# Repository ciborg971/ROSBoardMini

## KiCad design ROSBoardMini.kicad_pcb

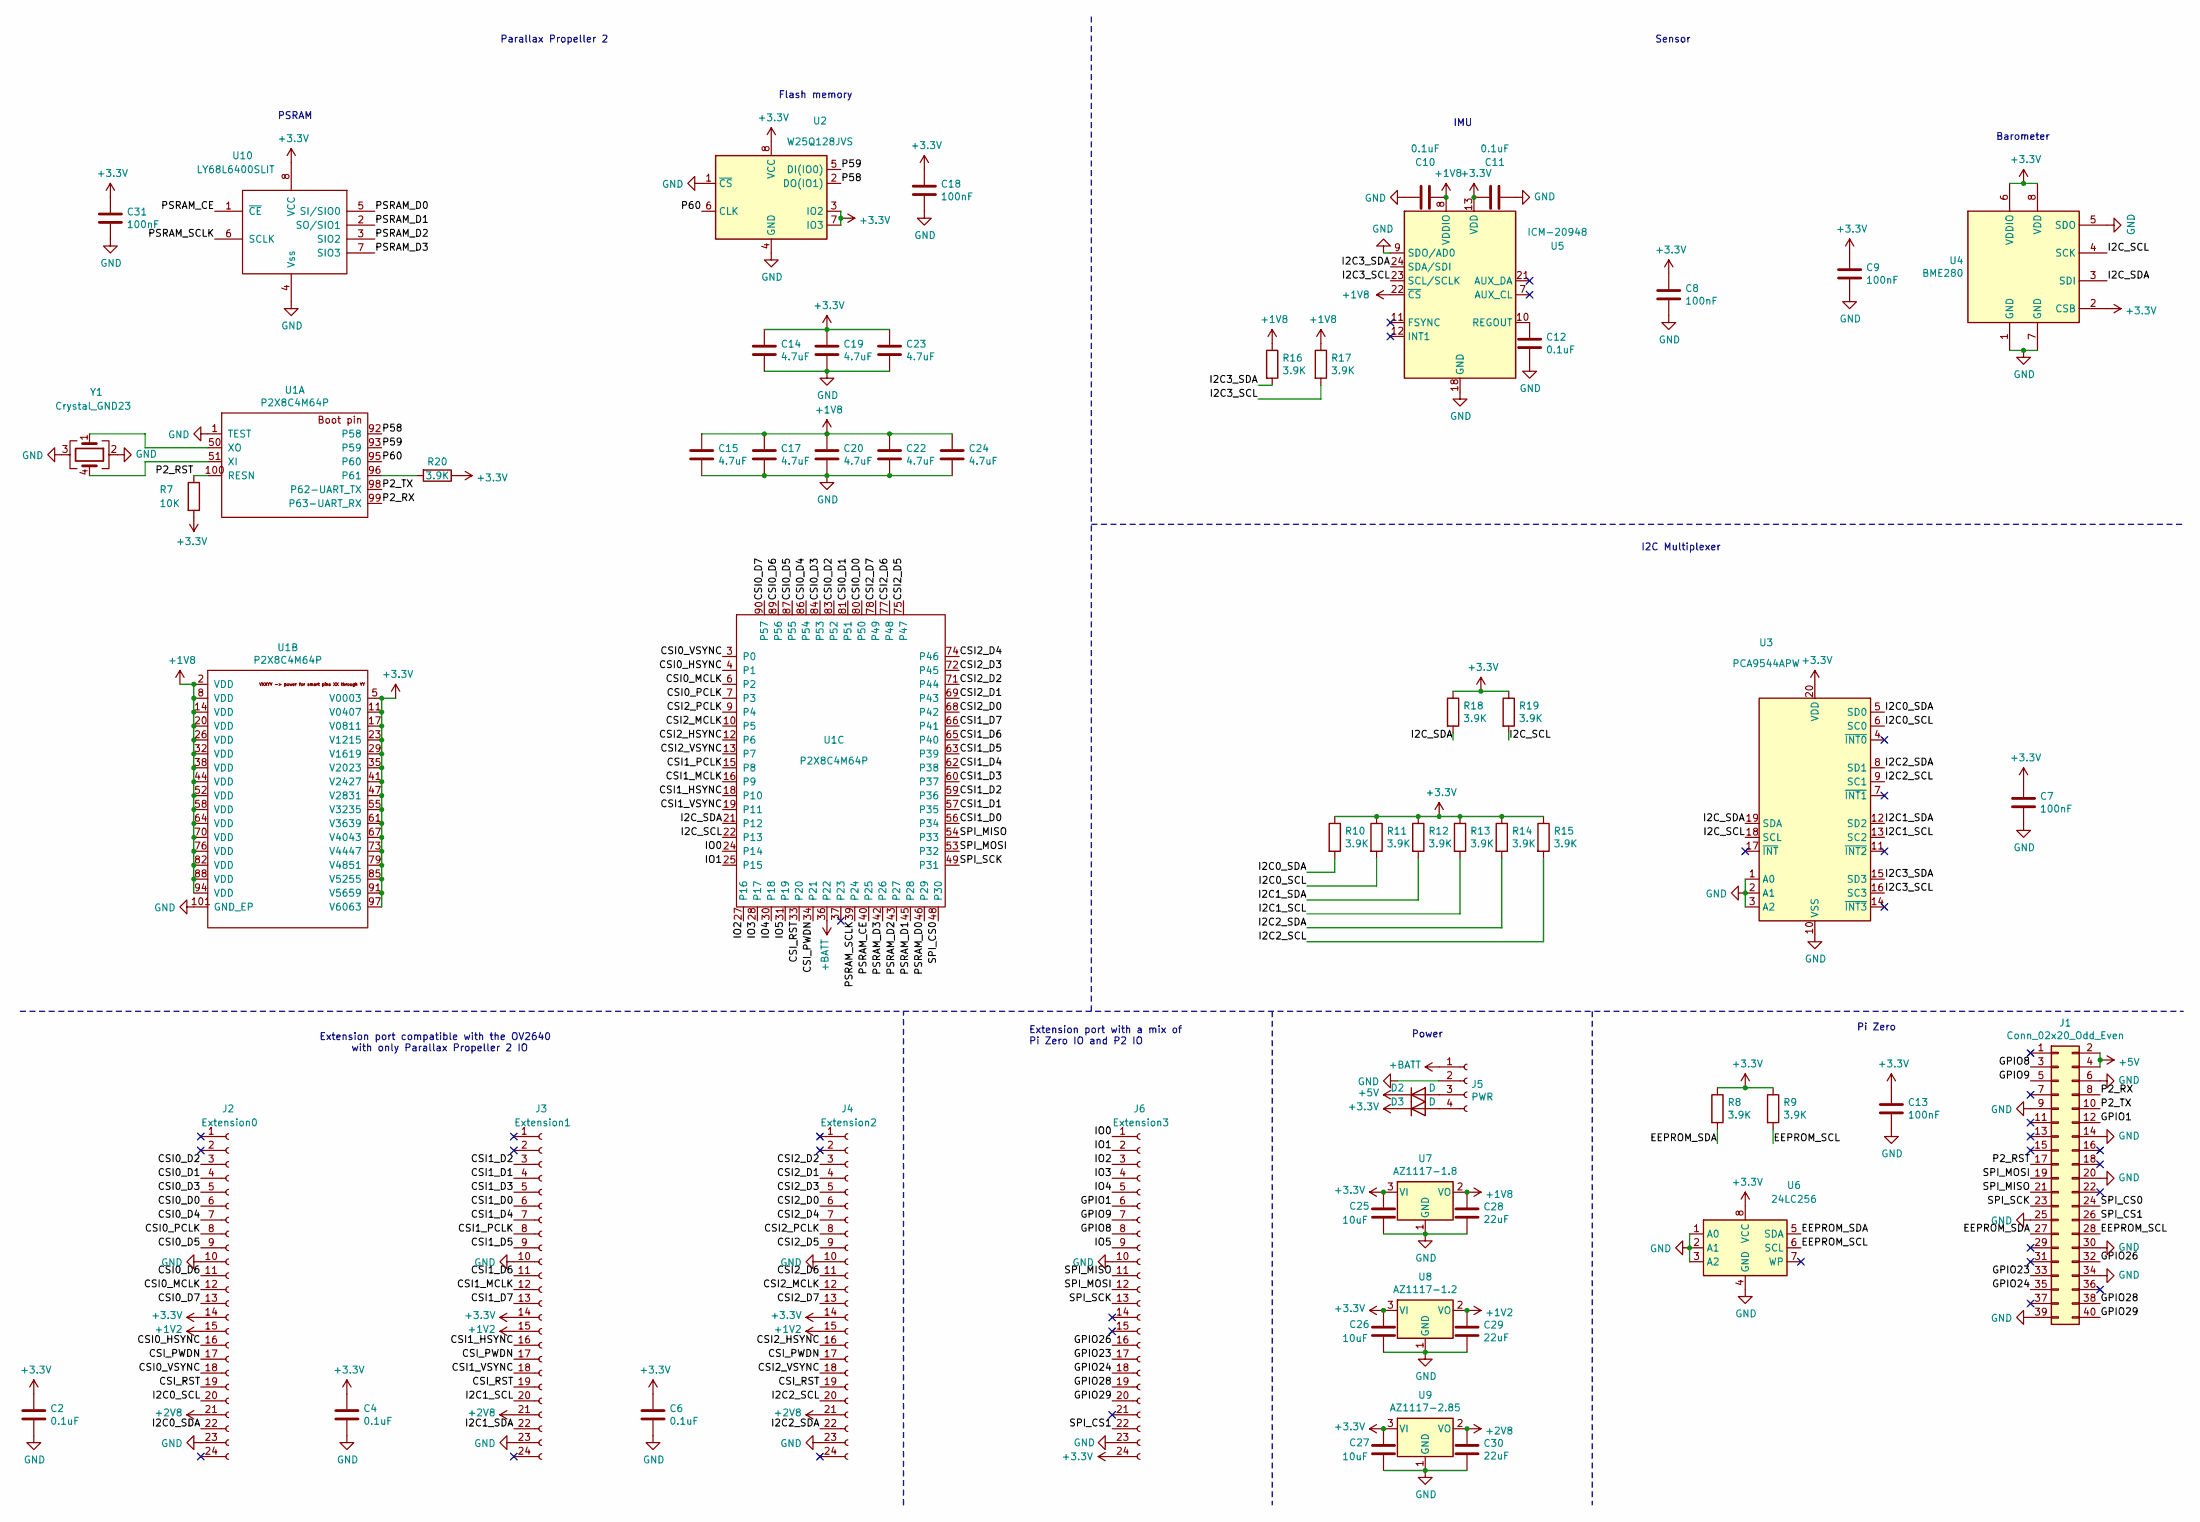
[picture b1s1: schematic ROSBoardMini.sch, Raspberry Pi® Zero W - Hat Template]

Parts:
C2, C4, C6, C10, C11, C12: 0.1uF; C_0402_1005Metric
C7, C8, C9, C13, C18, C31: 100nF; C_0402_1005Metric
C14, C15, C17, C19, C20, C22, C23, C24: 4.7uF; C_0402_1005Metric
C25, C26, C27: 10uF; C_0402_1005Metric
C28, C29, C30: 22uF; C_0402_1005Metric
D2, D3: D; D_0805_2012Metric
J1: Conn_02x20_Odd_Even; PinHeader_2x20_P2.54mm_Vertical
J2: Extension0; Hirose_FH12-24S-0.5SH_1x24-1MP_P0.50mm_Horizontal
J3: Extension1; Hirose_FH12-24S-0.5SH_1x24-1MP_P0.50mm_Horizontal
J4: Extension2; Hirose_FH12-24S-0.5SH_1x24-1MP_P0.50mm_Horizontal
J5: PWR; PinHeader_1x04_P2.54mm_Vertical
J6: Extension3; Hirose_FH12-24S-0.5SH_1x24-1MP_P0.50mm_Horizontal
R7: 10K; R_0201_0603Metric
R8, R9, R10, R11, R12, R13, R14, R15, R16, R17, R18, R19, R20: 3.9K; R_0201_0603Metric
U1: P2X8C4M64P; TQFP-100-1EP_14x14mm_P0.5mm_EP5x5mm
U2: W25Q128JVS; SOIC-8_5.23x5.23mm_P1.27mm
U3: PCA9544APW; TSSOP-20_4.4x6.5mm_P0.65mm
U4: BME280; Bosch_LGA-8_2.5x2.5mm_P0.65mm_ClockwisePinNumbering
U5: ICM-20948; InvenSense_QFN-24_3x3mm_P0.4mm
U6: 24LC256; TSSOP-8_4.4x3mm_P0.65mm
U7: AZ1117-1.8; SOT-89-3
U8: AZ1117-1.2; SOT-89-3
U9: AZ1117-2.85; SOT-89-3
U10: LY68L6400SLIT; SOP-8_3.9x4.9mm_P1.27mm
Y1: Crystal_GND23; Crystal_SMD_Abracon_ABM8G-4Pin_3.2x2.5mm

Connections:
+1V2: C29.1, J2.15, J3.15, J4.15, U8.2 (VO)
+1V8: C10.1, C15.1, C17.1, C20.1, C22.1, C24.1, C28.1, R16.1, R17.1, U1.2 (VDD), U1.8 (VDD), U1.14 (VDD), U1.20 (VDD), U1.26 (VDD), U1.32 (VDD), U1.38 (VDD), U1.44 (VDD), U1.52 (VDD), U1.58 (VDD), U1.64 (VDD), U1.70 (VDD), U1.76 (VDD), U1.82 (VDD), U1.88 (VDD), U1.94 (VDD), U5.8 (VDDIO), U5.22 (~CS), U7.2 (VO)
+5V: D2.1 (K), J1.2, J1.4
+BATT: J5.1, U1.36 (P22)
/CSI0_D0: J2.6, U1.80 (P50)
/CSI0_D1: J2.4, U1.81 (P51)
/CSI0_D2: J2.3, U1.83 (P52)
/CSI0_D3: J2.5, U1.84 (P53)
/CSI0_D4: J2.7, U1.86 (P54)
/CSI0_D5: J2.9, U1.87 (P55)
/CSI0_D6: J2.11, U1.89 (P56)
/CSI0_D7: J2.13, U1.90 (P57)
/CSI0_HSYNC: J2.16, U1.4 (P1)
/CSI0_MCLK: J2.12, U1.6 (P2)
/CSI0_PCLK: J2.8, U1.7 (P3)
/CSI0_VSYNC: J2.18, U1.3 (P0)
/CSI1_D0: J3.6, U1.56 (P34)
/CSI1_D1: J3.4, U1.57 (P35)
/CSI1_D2: J3.3, U1.59 (P36)
/CSI1_D3: J3.5, U1.60 (P37)
/CSI1_D4: J3.7, U1.62 (P38)
/CSI1_D5: J3.9, U1.63 (P39)
/CSI1_D6: J3.11, U1.65 (P40)
/CSI1_D7: J3.13, U1.66 (P41)
/CSI1_HSYNC: J3.16, U1.18 (P10)
/CSI1_MCLK: J3.12, U1.16 (P9)
/CSI1_PCLK: J3.8, U1.15 (P8)
/CSI1_VSYNC: J3.18, U1.19 (P11)
/CSI2_D0: J4.6, U1.68 (P42)
/CSI2_D1: J4.4, U1.69 (P43)
/CSI2_D2: J4.3, U1.71 (P44)
/CSI2_D3: J4.5, U1.72 (P45)
/CSI2_D4: J4.7, U1.74 (P46)
/CSI2_D5: J4.9, U1.75 (P47)
/CSI2_D6: J4.11, U1.77 (P48)
/CSI2_D7: J4.13, U1.78 (P49)
/CSI2_HSYNC: J4.16, U1.12 (P6)
/CSI2_MCLK: J4.12, U1.10 (P5)
/CSI2_PCLK: J4.8, U1.9 (P4)
/CSI2_VSYNC: J4.18, U1.13 (P7)
/CSI_PWDN: J2.17, J3.17, J4.17, U1.34 (P21)
/CSI_RST: J2.19, J3.19, J4.19, U1.33 (P20)
/EEPROM_SCL: J1.28, R9.2, U6.6 (SCL)
/EEPROM_SDA: J1.27, R8.2, U6.5 (SDA)
/GPIO1: J1.12, J6.6
/GPIO8: J1.3, J6.8
/GPIO9: J1.5, J6.7
/GPIO23: J1.33, J6.17
/GPIO24: J1.35, J6.18
/GPIO26: J1.32, J6.16
/GPIO28: J1.38, J6.19
/GPIO29: J1.40, J6.20
/I2C0_SCL: J2.20, R11.2, U3.6 (SC0)
/I2C0_SDA: J2.22, R10.2, U3.5 (SD0)
/I2C1_SCL: J3.20, R13.2, U3.13 (SC2)
/I2C1_SDA: J3.22, R12.2, U3.12 (SD2)
/I2C2_SCL: J4.20, R15.2, U3.9 (SC1)
/I2C2_SDA: J4.22, R14.2, U3.8 (SD1)
/I2C3_SCL: R17.2, U3.16 (SC3), U5.23 (SCL/SCLK)
/I2C3_SDA: R16.2, U3.15 (SD3), U5.24 (SDA/SDI)
/I2C_SCL: R19.2, U1.22 (P13), U3.18 (SCL), U4.4 (SCK)
/I2C_SDA: R18.2, U1.21 (P12), U3.19 (SDA), U4.3 (SDI)
/IO0: J6.1, U1.24 (P14)
/IO1: J6.2, U1.25 (P15)
/IO2: J6.3, U1.27 (P16)
/IO3: J6.4, U1.28 (P17)
/IO4: J6.5, U1.30 (P18)
/IO5: J6.9, U1.31 (P19)
/P2_RST: J1.17, R7.1, U1.100 (RESN)
/P2_RX: J1.8, U1.99 (P63-UART_RX)
/P2_TX: J1.10, U1.98 (P62-UART_TX)
/P58: U1.92 (P58), U2.2 (DO(IO1))
/P59: U1.93 (P59), U2.5 (DI(IO0))
/P60: U1.95 (P60), U2.6 (CLK)
/PSRAM_CE: U1.40 (P25), U10.1 (~CE)
/PSRAM_D0: U1.46 (P29), U10.5 (SI/SIO0)
/PSRAM_D1: U1.45 (P28), U10.2 (SO/SIO1)
/PSRAM_D2: U1.43 (P27), U10.3 (SIO2)
/PSRAM_D3: U1.42 (P26), U10.7 (SIO3)
/PSRAM_SCLK: U1.39 (P24), U10.6 (SCLK)
/SPI_CS0: J1.24, U1.48 (P30)
/SPI_CS1: J1.26, J6.22
/SPI_MISO: J1.21, J6.11, U1.54 (P33)
/SPI_MOSI: J1.19, J6.12, U1.53 (P32)
/SPI_SCK: J1.23, J6.13, U1.49 (P31)
unnamed 85: U9.6; also elsewhere on the board
unnamed: C12.1, U5.10 (REGOUT)
unnamed: D2.2 (A), J5.3
unnamed: D3.2 (A), J5.4
unnamed: R20.2, U1.96 (P61)
unnamed: U1.50 (XO), Y1.1
unnamed: U1.51 (XI), Y1.4

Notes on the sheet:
Extension port compatible with the OV2640 with only Parallax Propeller 2 IO
Extension port with a mix of Pi Zero IO and P2 IO
Power
I2C Multiplexer
Sensor
Pi Zero
Parallax Propeller 2
Flash memory
PSRAM
Barometer
IMU

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
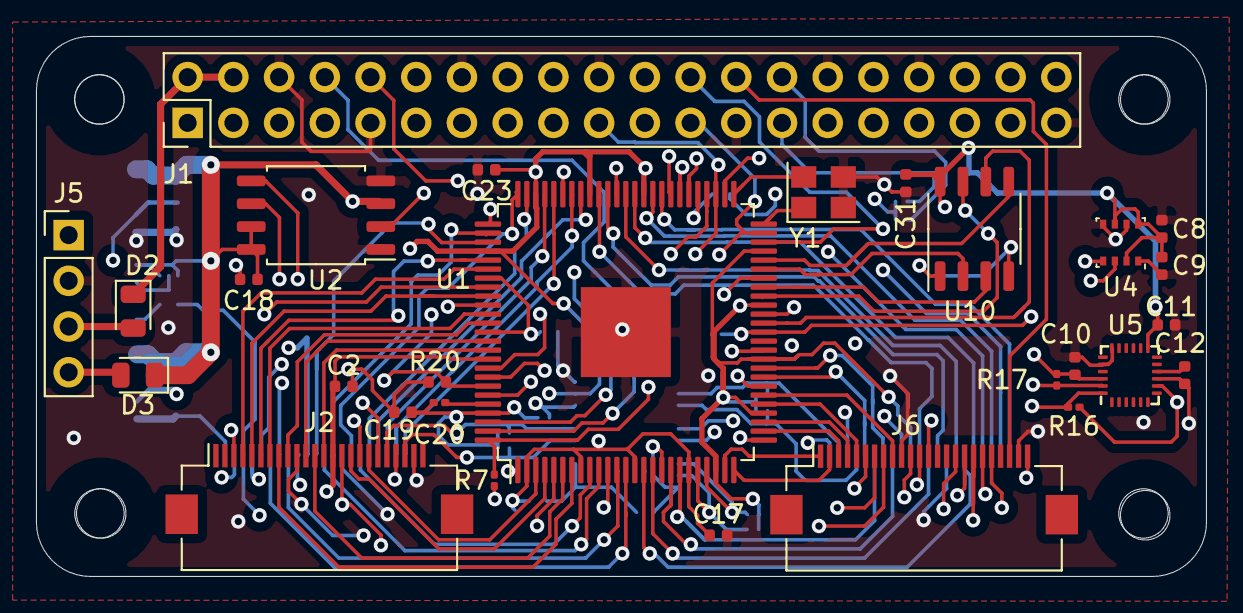
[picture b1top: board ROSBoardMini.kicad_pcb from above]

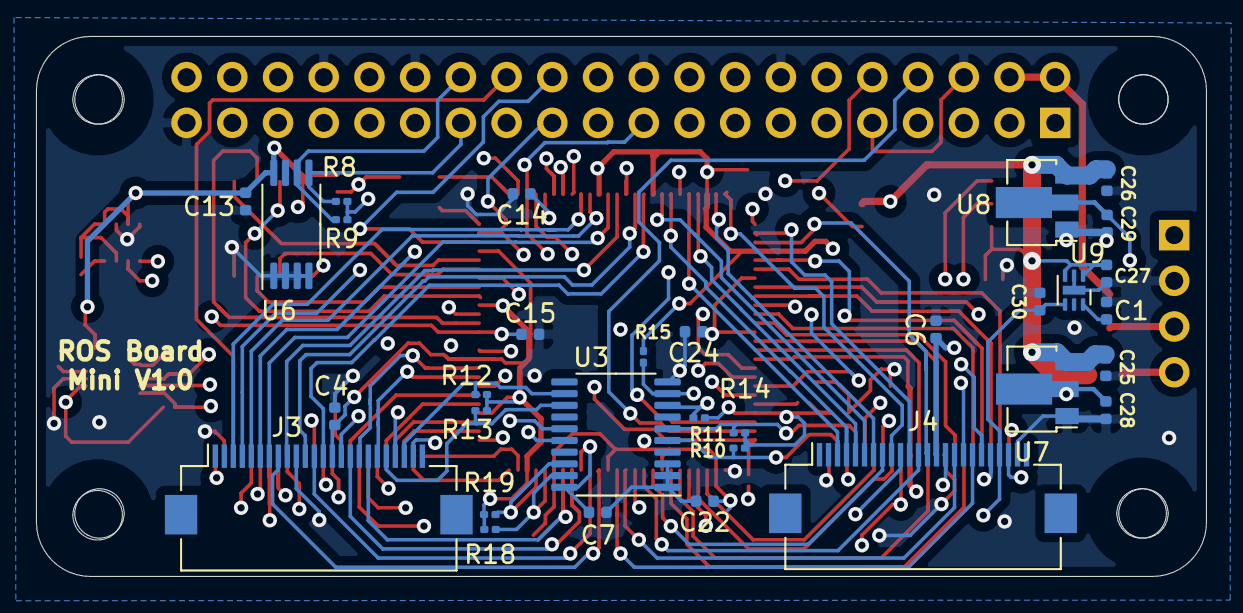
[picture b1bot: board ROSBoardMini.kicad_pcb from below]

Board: 4 copper layers, 65.0 x 30.0 mm, 60 parts (32 on the bottom side), 95 nets.

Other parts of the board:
C1: 0.1uF; C_0402_1005Metric

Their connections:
unnamed 85: C1.1; also elsewhere on the board

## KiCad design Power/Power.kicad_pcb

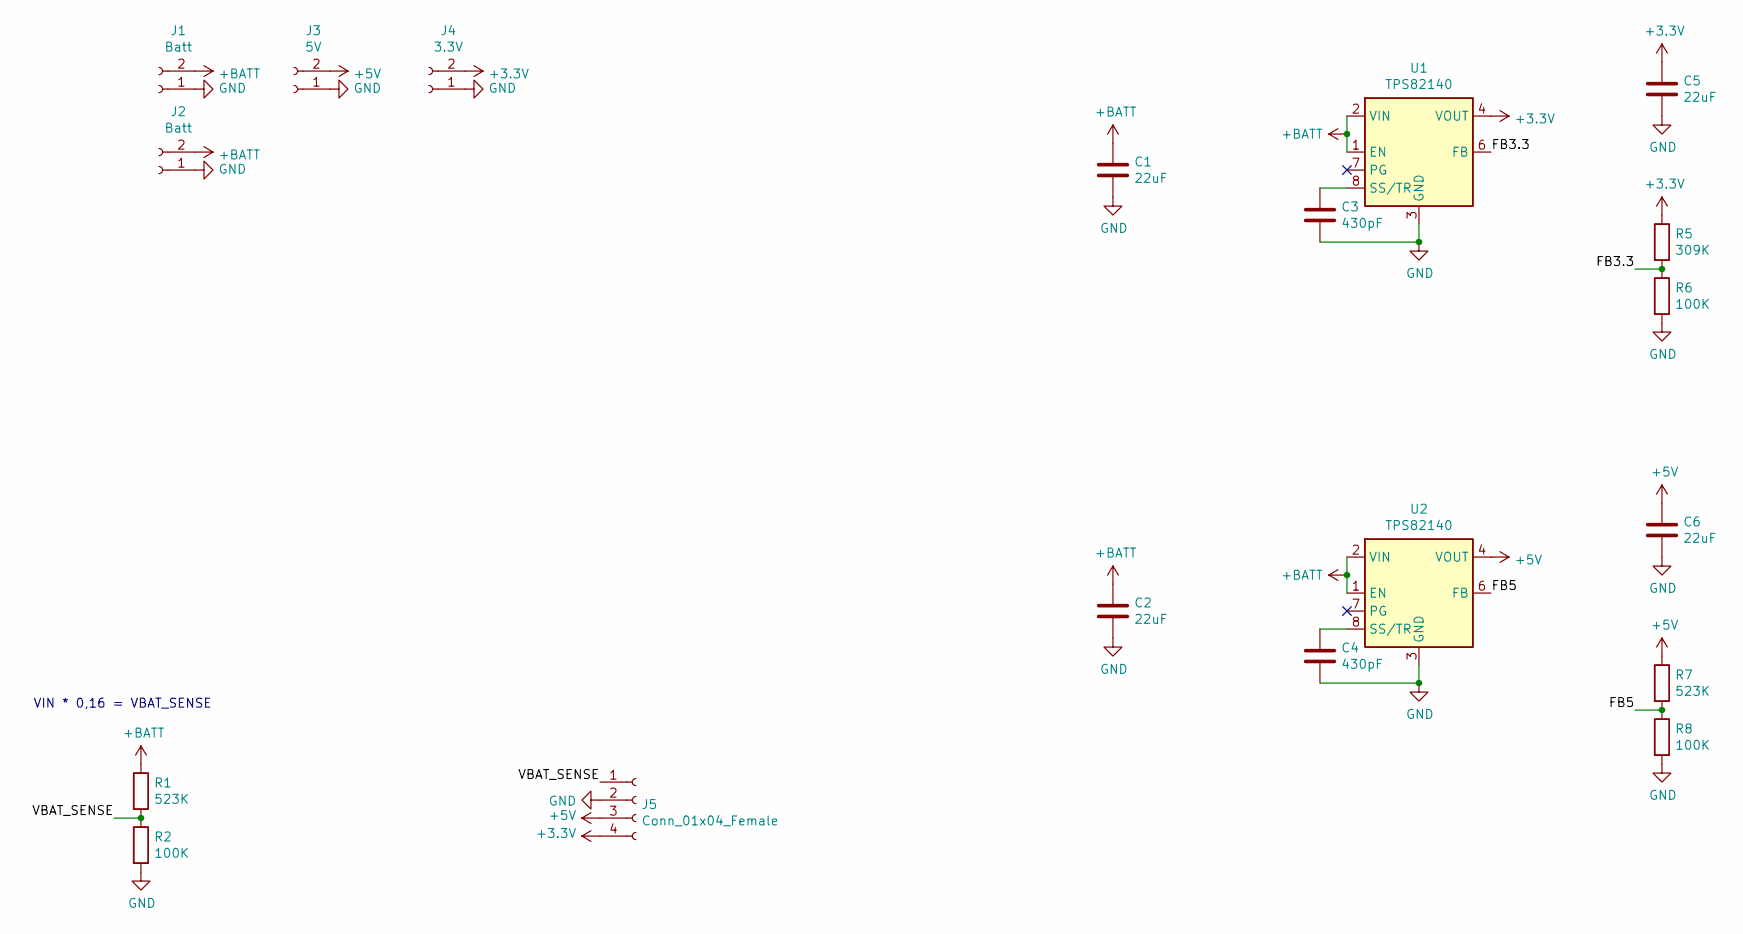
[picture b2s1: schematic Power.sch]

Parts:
C1, C2, C5, C6: 22uF; C_0402_1005Metric
C3, C4: 430pF; C_0402_1005Metric
J1, J2: Batt; PinSocket_1x02_P2.54mm_Vertical
J3: 5V; PinSocket_1x02_P2.54mm_Vertical
J4: 3.3V; PinSocket_1x02_P2.54mm_Vertical
J5: Conn_01x04_Female; PinSocket_1x04_P2.54mm_Vertical
R1, R7: 523K; R_0402_1005Metric
R2, R6, R8: 100K; R_0402_1005Metric
R5: 309K; R_0402_1005Metric
U1, U2: TPS82140; Texas_SIL0008D_MicroSiP-8-1EP_2.8x3mm_P0.65mm_EP1.1x1.9mm_T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

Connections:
+3V3: C5.1, J4.2, J5.4, R5.1, U1.4 (VOUT), U1.5 (VOUT)
+5V: C6.1, J3.2, J5.3, R7.1, U2.4 (VOUT), U2.5 (VOUT)
+BATT: C1.1, C2.1, J1.2, J2.2, R1.1, U1.1 (EN), U1.2 (VIN), U2.1 (EN), U2.2 (VIN)
/FB3.3: R5.2, R6.1, U1.6 (FB)
/FB5: R7.2, R8.1, U2.6 (FB)
/VBAT_SENSE: J5.1, R1.2, R2.1
GND: C1.2, C2.2, C3.2, C4.2, C5.2, C6.2, J1.1, J2.1, J3.1, J4.1, J5.2, R2.2, R6.2, R8.2, U1.3 (GND), U1.9 (GND), U2.3 (GND), U2.9 (GND)
unnamed: C3.1, U1.8 (SS/TR)
unnamed: C4.1, U2.8 (SS/TR)

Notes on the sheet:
VIN * 0,16 = VBAT_SENSE

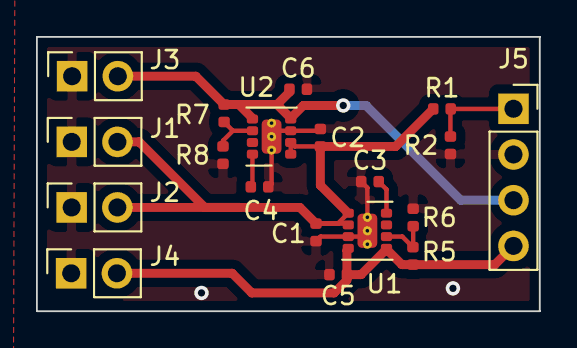
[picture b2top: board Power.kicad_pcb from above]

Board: 2 copper layers, 27.9 x 15.2 mm, 19 parts (0 on the bottom side), 9 nets.

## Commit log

2020-10-29 add lib and doc
2020-10-29 Rooting progress
2020-11-02 Re arrange pin to allow 1 cog to use 3 camera + rooting progress
2020-11-02 Everything rooted except power
2020-11-02 Extension board for breadboard
2020-11-03 Rooting done
2020-11-04 Power board done
2020-11-04 Clean schematic and rename 4th connector
2020-11-05 Various cleaning, doc in schematic and replaced problematic 2.8V ldo
2020-11-08 Add crystal reference

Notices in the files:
ROSBoardMini.kicad_pcb:
License: MIT - Copyright 2018 StudioPieters®
